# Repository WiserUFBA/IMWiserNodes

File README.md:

# IMWiserNodes
Repository with the codes and boards of IMWiserNode project

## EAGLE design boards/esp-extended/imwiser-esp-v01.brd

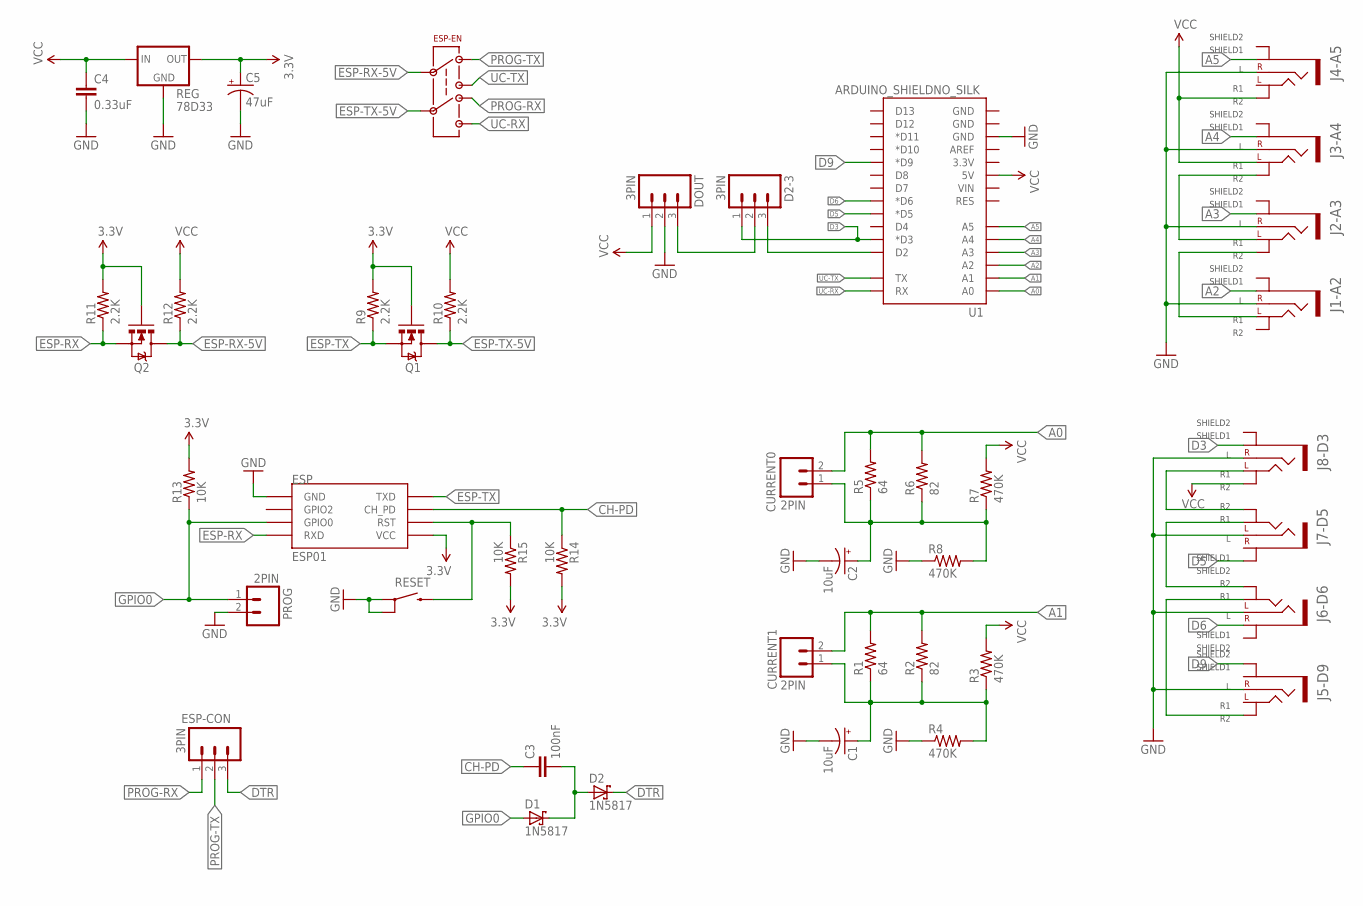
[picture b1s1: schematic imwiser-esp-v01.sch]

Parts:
C1, C2: 10uF; CPOL-RADIAL-10UF-25V
C3: 100nF; CAP-PTH-SMALL
C4: 0.33uF; CAP-PTH-SMALL
C5: 47uF; CPOL-RADIAL-10UF-25V
CURRENT0, CURRENT1: 2PIN; 1X02
D1, D2: 1N5817; DO41-7
D2-3: 3PIN; 1X03
DOUT: 3PIN; 1X03
ESP: ESP01
ESP-CON: 3PIN; 1X03
ESP-EN: DPDT-GENERIC-SWITCH-7X7MM; DPDT-PTH-7*7MM
J1-A2, J2-A3, J3-A4, J4-A5, J5-D9, J6-D6, J7-D5, J8-D3: PJ-313-SPAD; PJ-313-5PIN-SMALL
PROG: 2PIN; 1X02
Q1, Q2: MOSFET-NCHANNEL2N7000; TO-92
R1, R5: 64; 0207/10
R2, R6: 82; 0207/10
R3, R4, R7, R8: 470K; 0207/10
R9, R10, R11, R12: 2.2K; 0207/10
R13, R14, R15: 10K; 0207/10
REG: 78D33; TO220-IGO
RESET: SWITCH-MOMENTARY-2PTH; TACTILE-PTH
U1: ARDUINO_SHIELDNO_SILK; DUEMILANOVE_VIAS

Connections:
3.3V: C5.1 (+), ESP.VCC, Q1.2 (G), Q2.2 (G), R9.2, R11.2, R13.2, R14.2, R15.2, REG.OUT
A0: CURRENT0.2, R5.2, R6.2, U1.A0
A1: CURRENT1.2, R1.2, R2.2, U1.A1
A2: J1-A2.1.1 (SHIELD1), U1.A2
A3: J2-A3.1.1 (SHIELD1), U1.A3
A4: J3-A4.1.1 (SHIELD1), U1.A4
A5: J4-A5.1.1 (SHIELD1), U1.A5
BURDEN-C0: C2.1 (+), CURRENT0.1, R5.1, R6.1, R7.1, R8.2
BURDEN-C1: C1.1 (+), CURRENT1.1, R1.1, R2.1, R3.1, R4.2
CH-PD: C3.1, ESP.CH_PD, R14.1
D3: D2-3.1, J8-D3.1.1 (SHIELD1), U1.D3 (*D3)
D5: J7-D5.1.2 (SHIELD2), U1.D5 (*D5)
D6: J6-D6.1.1 (SHIELD1), U1.D6 (*D6)
D9: J5-D9.1.2 (SHIELD2), U1.D9 (*D9)
DTR: D2.C, ESP-CON.3
ESP-RX: ESP.RX (RXD), Q2.1 (S), R11.1
ESP-RX-5V: ESP-EN.3-IN1 (IN1), Q2.3 (D), R12.1
ESP-TX: ESP.TX (TXD), Q1.1 (S), R9.1
ESP-TX-5V: ESP-EN.4-IN2 (IN2), Q1.3 (D), R10.1
GND: C1.2 (-), C2.2 (-), C4.2, C5.2 (-), DOUT.2, ESP.GND, J1-A2.2 (R), J2-A3.2 (R), J3-A4.2 (R), J4-A5.2 (R), J5-D9.2 (R), J6-D6.2 (R), J7-D5.2 (R), J8-D3.2 (R), PROG.2, R4.1, R8.1, REG.GND, RESET.1, RESET.2, U1.GND@2 (GND)
GPIO0: D1.A, ESP.GPIO0, PROG.1, R13.1
unnamed: J2-A3.3.1 (L1), J3-A4.3.2 (L2)
unnamed: J1-A2.3.1 (L1), J2-A3.3.2 (L2)
unnamed: J7-D5.3.2 (L2), J8-D3.3.1 (L1)
unnamed: D2-3.2, DOUT.3
unnamed: J6-D6.3.2 (L2), J7-D5.3.1 (L1)
unnamed: D2-3.3, U1.D2
unnamed: J5-D9.3.2 (L2), J6-D6.3.1 (L1)
PROG-RX: ESP-CON.1, ESP-EN.2-OUT2-A (OUT2-A)
PROG-TX: ESP-CON.2, ESP-EN.1-OUT1-A (OUT1-A)
RST: ESP.RST, R15.1, RESET.3 (2)
U$1: C3.2, D1.C, D2.A
UC-RX: ESP-EN.6-OUT2-B (OUT2-B), U1.RX
UC-TX: ESP-EN.5-OUT1-B (OUT1-B), U1.TX
VCC: C4.1, DOUT.1, J3-A4.3.1 (L1), J4-A5.3.2 (L2), J8-D3.3.2 (L2), R3.2, R7.2, R10.2, R12.2, REG.IN, U1.5V

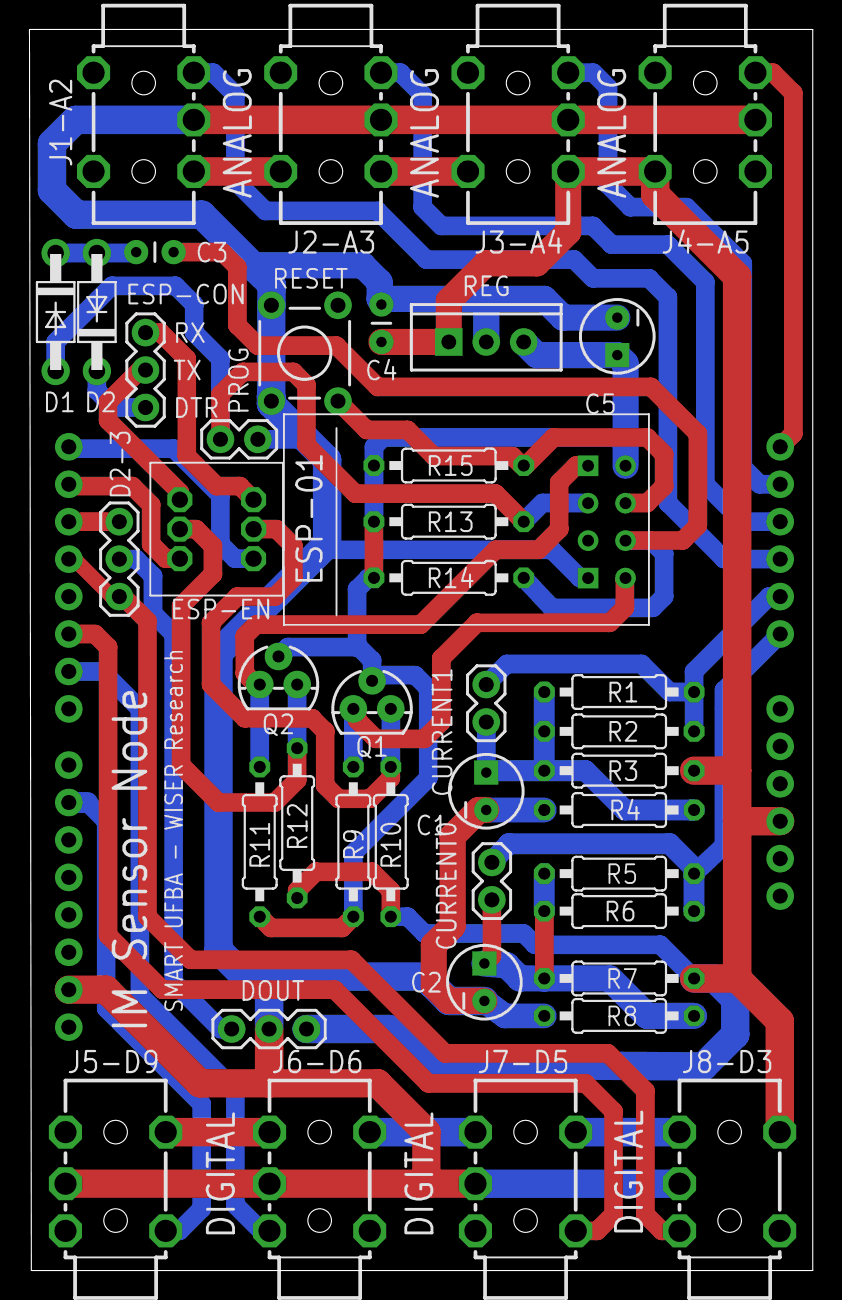
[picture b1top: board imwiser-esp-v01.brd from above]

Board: 2 copper layers, 53.1 x 84.2 mm, 43 parts (0 on the bottom side), 35 nets.

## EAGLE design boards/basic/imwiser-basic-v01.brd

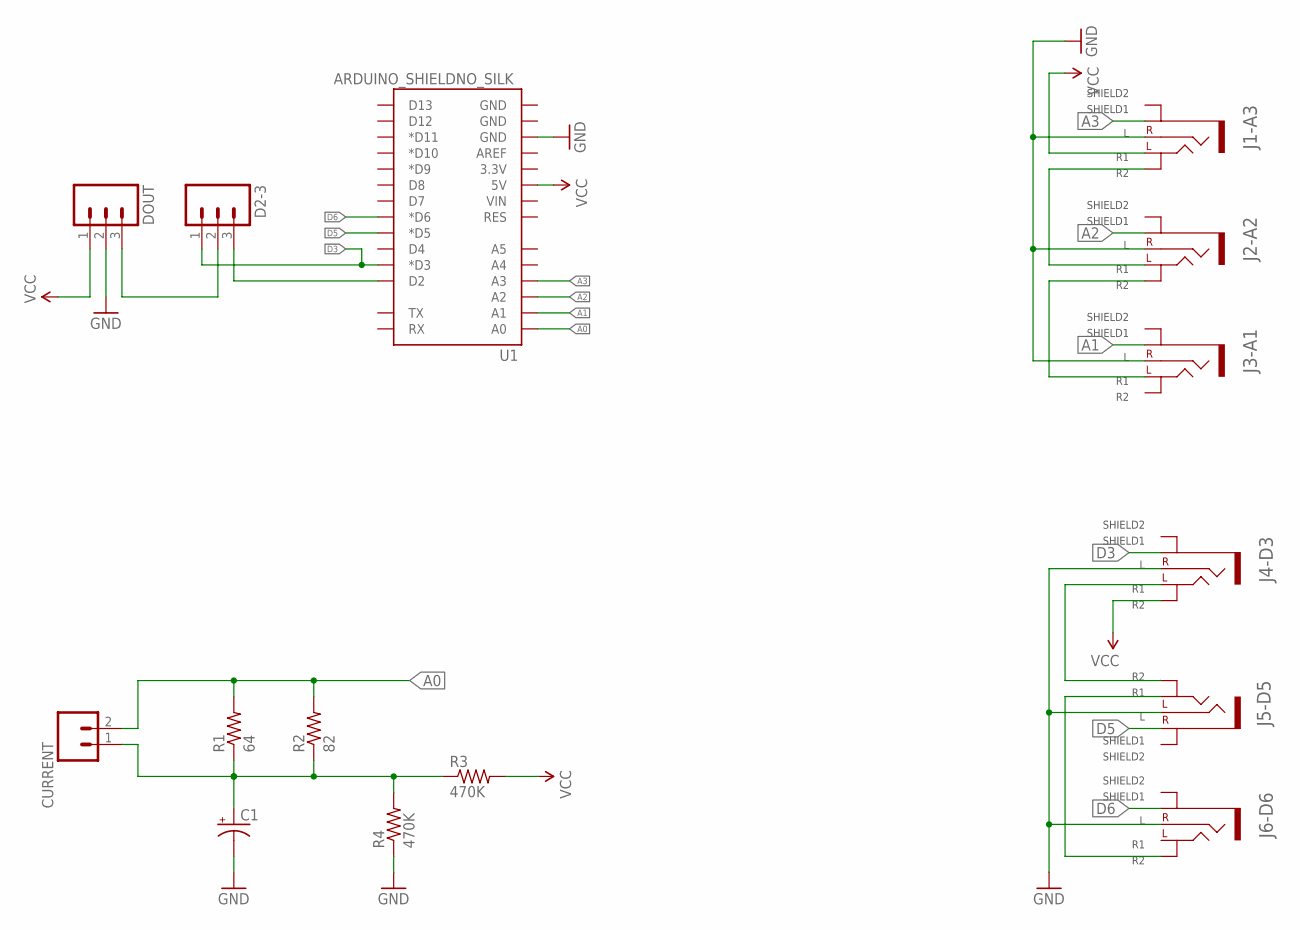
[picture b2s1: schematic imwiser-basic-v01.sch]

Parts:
C1: 10UF-25V-20%(PTH); CPOL-RADIAL-10UF-25V
CURRENT: M02PTH; 1X02
D2-3: M03PTH; 1X03
DOUT: M03PTH; 1X03
J1-A3, J2-A2, J3-A1, J4-D3, J5-D5, J6-D6: PJ-313-SPAD; PJ-313-5PIN-SMALL
R1: 64; 0207/10
R2: 82; 0207/10
R3, R4: 470K; 0207/10
U1: ARDUINO_SHIELDNO_SILK; DUEMILANOVE_VIAS

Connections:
A0: CURRENT.2, R1.2, R2.2, U1.A0
A1: J3-A1.1.1 (SHIELD1), U1.A1
A2: J2-A2.1.1 (SHIELD1), U1.A2
A3: J1-A3.1.1 (SHIELD1), U1.A3
BURDEN-C0: C1.1 (+), CURRENT.1, R1.1, R2.1, R3.1, R4.2
D2: D2-3.3, U1.D2
D3: D2-3.1, J4-D3.1.1 (SHIELD1), U1.D3 (*D3)
D5: J5-D5.1.1 (SHIELD1), U1.D5 (*D5)
D6: J6-D6.1.1 (SHIELD1), U1.D6 (*D6)
GND: C1.2 (-), DOUT.2, J1-A3.2 (R), J2-A2.2 (R), J3-A1.2 (R), J4-D3.2 (R), J5-D5.2 (R), J6-D6.2 (R), R4.1, U1.GND@2 (GND)
unnamed: J1-A3.3.2 (L2), J2-A2.3.1 (L1)
unnamed: J2-A2.3.2 (L2), J3-A1.3.1 (L1)
unnamed: J4-D3.3.1 (L1), J5-D5.3.2 (L2)
unnamed: J5-D5.3.1 (L1), J6-D6.3.2 (L2)
OPTION-D2-3: D2-3.2, DOUT.3
VCC: DOUT.1, J1-A3.3.1 (L1), J4-D3.3.2 (L2), R3.2, U1.5V

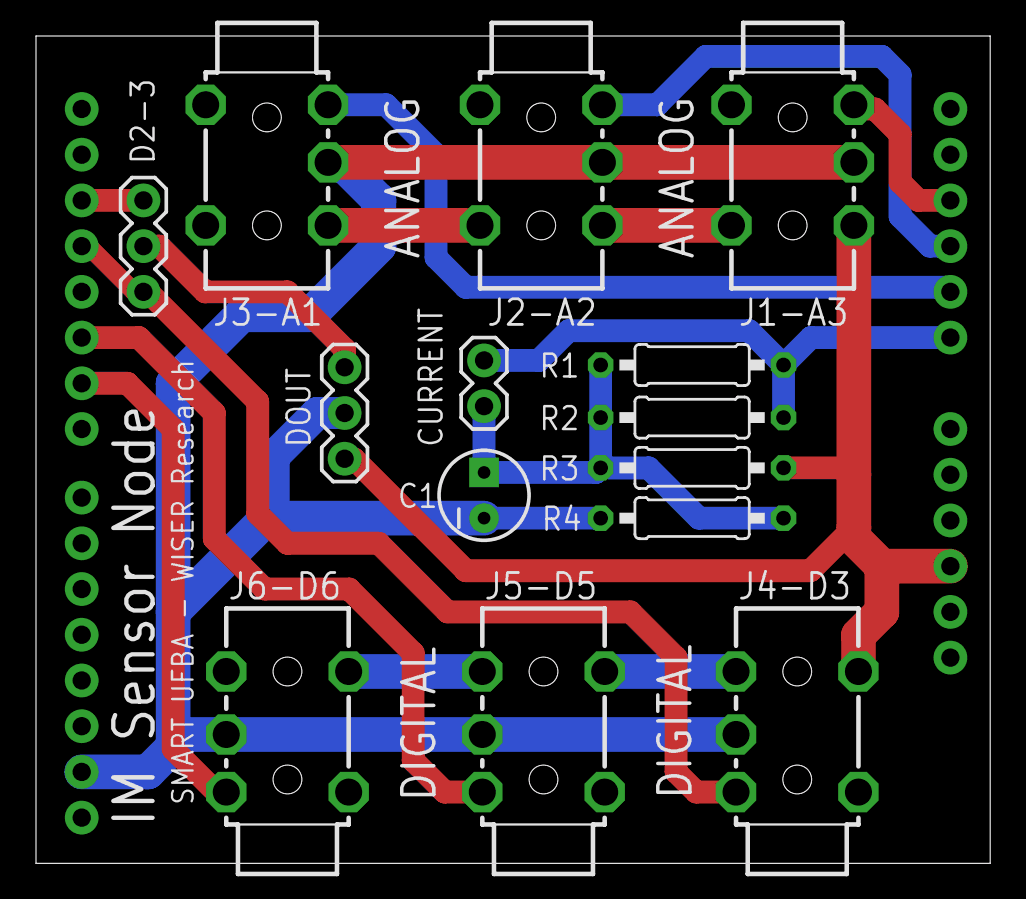
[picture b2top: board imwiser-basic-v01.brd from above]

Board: 2 copper layers, 53.0 x 46.0 mm, 15 parts (0 on the bottom side), 16 nets.

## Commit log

2016-02-08 IM Sensor node v0.1
2016-02-08 IM Sensor Node v0.2
2016-02-23 New beta version of IMSensor+Actuator+Current Sensor ESP8266 Beta
2016-02-23 Finished first layout
2016-02-23 Moved libraries to libraries folder
2016-02-23 Moved boards to boards folder
2016-02-24 Cleaned and organized IMSensor for ESP8266 V1
2016-02-24 Organized files, left organize cam jobs and libraries
2016-02-26 Finished version 0.1 of imwiser for ESP

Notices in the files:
parts and their libraries:
SparkFun-Boards: Licensing: Creative Commons ShareAlike 4.0 International - https://creativecommons.org/licenses/by-sa/4.0
